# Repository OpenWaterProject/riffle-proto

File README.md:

# riffle_328-proto

The Riffle_328 protoboard is intended to simplify the process of prototyping simple circuits and connecting them to the Riffle_328.  

By plugging it into the 2x7 connector on the end of the Riffle provides access to all 14 pins on the end of the Riffle

- A0
- A1
- A2
- D2
- D3
- D10
- D11
- D12
- SCL
- SDA
- 3v3
- Ground
- Battery voltage

Holes are not connected along the longest dimension of the protoboard; the holes *are* connected with small surface traces along the shortest dimension of the board, but these traces can be cut with a knife if needed.

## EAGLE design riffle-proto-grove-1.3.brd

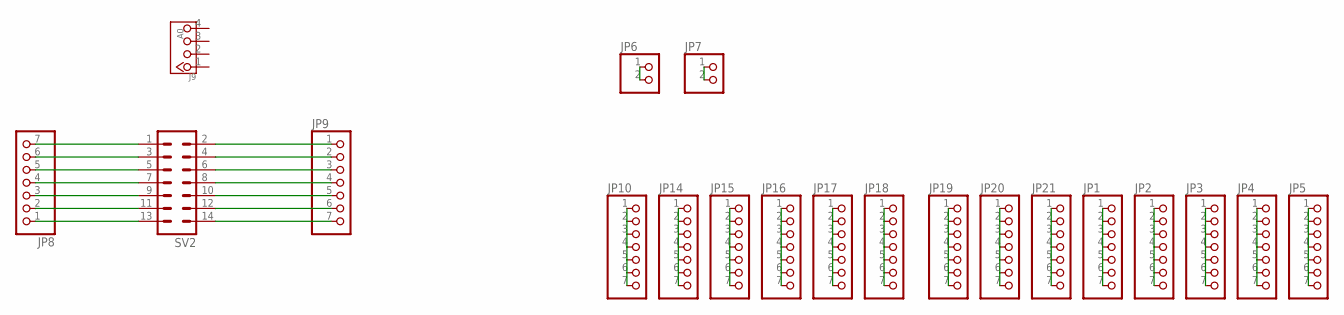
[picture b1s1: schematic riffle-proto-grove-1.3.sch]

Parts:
J9: A0; 4P-2.0-90D
JP1, JP2, JP3, JP4, JP5, JP8, JP9, JP10, JP14, JP15, JP16, JP17, JP18, JP19, JP20, JP21: HEADER-1X770MIL; 1X07_ROUND_70
JP6, JP7: HEADER-1X2ROUND; 1X02_ROUND
SV2: MA07-2

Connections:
D3: JP9.5, SV2.10
GND: JP9.7, SV2.14
unnamed: JP8.1, SV2.13
unnamed: JP8.2, SV2.11
unnamed: JP8.3, SV2.9
unnamed: JP8.4, SV2.7
unnamed: JP8.5, SV2.5
unnamed: JP8.6, SV2.3
unnamed: JP8.7, SV2.1
unnamed: JP10.1, JP10.2, JP10.3, JP10.4, JP10.5, JP10.6, JP10.7
unnamed: JP14.1, JP14.2, JP14.3, JP14.4, JP14.5, JP14.6, JP14.7
unnamed: JP9.3, SV2.6
unnamed: JP9.4, SV2.8
unnamed: JP15.1, JP15.2, JP15.3, JP15.4, JP15.5, JP15.6, JP15.7
unnamed: JP16.1, JP16.2, JP16.3, JP16.4, JP16.5, JP16.6, JP16.7
unnamed: JP17.1, JP17.2, JP17.3, JP17.4, JP17.5, JP17.6, JP17.7
unnamed: JP18.1, JP18.2, JP18.3, JP18.4, JP18.5, JP18.6, JP18.7
unnamed: JP19.1, JP19.2, JP19.3, JP19.4, JP19.5, JP19.6, JP19.7
unnamed: JP20.1, JP20.2, JP20.3, JP20.4, JP20.5, JP20.6, JP20.7
unnamed: JP21.1, JP21.2, JP21.3, JP21.4, JP21.5, JP21.6, JP21.7
unnamed: JP1.1, JP1.2, JP1.3, JP1.4, JP1.5, JP1.6, JP1.7
unnamed: JP2.1, JP2.2, JP2.3, JP2.4, JP2.5, JP2.6, JP2.7
unnamed: JP3.1, JP3.2, JP3.3, JP3.4, JP3.5, JP3.6, JP3.7
unnamed: JP4.1, JP4.2, JP4.3, JP4.4, JP4.5, JP4.6, JP4.7
unnamed: JP5.1, JP5.2, JP5.3, JP5.4, JP5.5, JP5.6, JP5.7
unnamed: JP6.1, JP6.2
unnamed: JP7.1, JP7.2
SCL: JP9.2, SV2.4
SDA: JP9.1, SV2.2
VCC: JP9.6, SV2.12

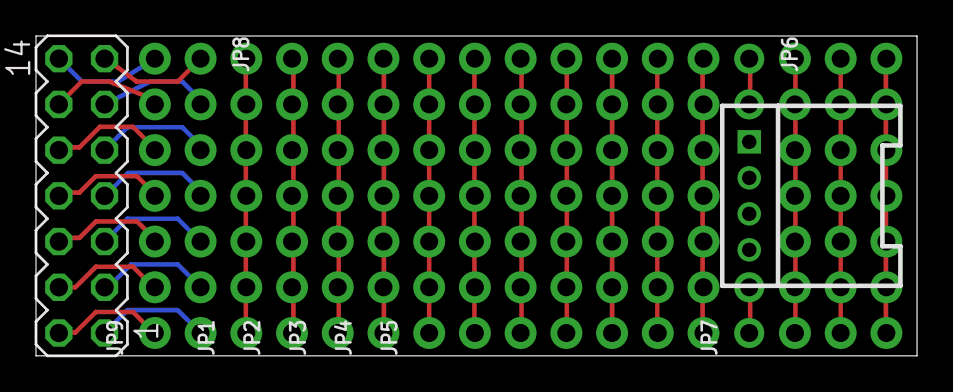
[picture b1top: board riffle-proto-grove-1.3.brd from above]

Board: 2 copper layers, 48.9 x 17.8 mm, 20 parts (0 on the bottom side), 30 nets.

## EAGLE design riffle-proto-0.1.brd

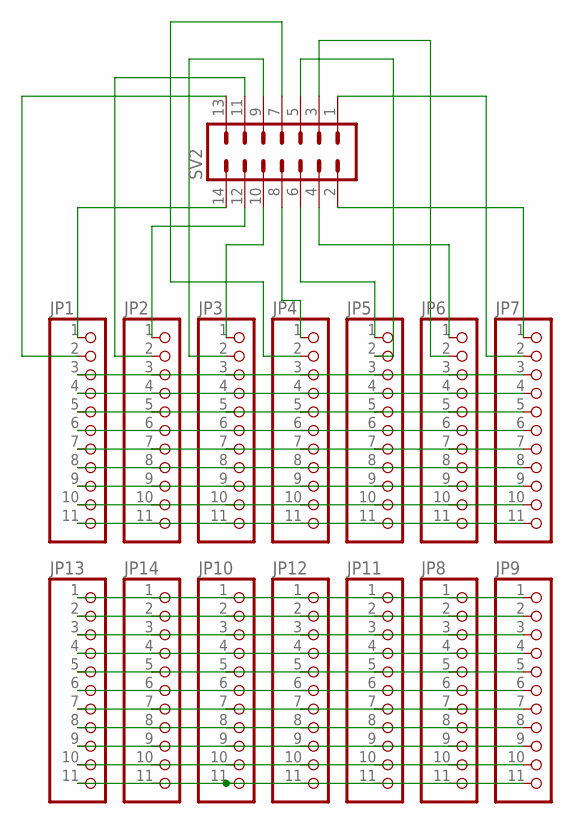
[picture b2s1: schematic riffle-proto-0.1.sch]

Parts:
JP1, JP2, JP3, JP4, JP5, JP6, JP7, JP8, JP9, JP10, JP11, JP12, JP13, JP14: HEADER-1X1176MIL; 1X11_ROUND_76
SV2: MA07-2

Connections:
unnamed: JP1.1, SV2.14
unnamed: JP2.1, SV2.12
unnamed: JP3.1, SV2.10
unnamed: JP4.1, SV2.8
unnamed: JP5.1, SV2.6
unnamed: JP6.1, SV2.4
unnamed: JP7.1, SV2.2
unnamed: JP1.2, SV2.13
unnamed: JP2.2, SV2.11
unnamed: JP3.2, SV2.9
unnamed: JP4.2, SV2.7
unnamed: JP5.2, SV2.5
unnamed: JP6.2, SV2.3
unnamed: JP7.2, SV2.1
unnamed: JP1.3, JP2.3, JP3.3, JP4.3, JP5.3, JP6.3, JP7.3
unnamed: JP1.4, JP2.4, JP3.4, JP4.4, JP5.4, JP6.4, JP7.4
unnamed: JP1.5, JP2.5, JP3.5, JP4.5, JP5.5, JP6.5, JP7.5
unnamed: JP1.6, JP2.6, JP3.6, JP4.6, JP5.6, JP6.6, JP7.6
unnamed: JP1.7, JP2.7, JP3.7, JP4.7, JP5.7, JP6.7, JP7.7
unnamed: JP1.8, JP2.8, JP3.8, JP4.8, JP5.8, JP6.8, JP7.8
unnamed: JP1.9, JP2.9, JP3.9, JP4.9, JP5.9, JP6.9, JP7.9
unnamed: JP1.10, JP2.10, JP3.10, JP4.10, JP5.10, JP6.10, JP7.10
unnamed: JP1.11, JP2.11, JP4.11, JP5.11, JP6.11, JP7.11
unnamed: JP8.1, JP9.1, JP10.1, JP11.1, JP12.1, JP13.1, JP14.1
unnamed: JP8.2, JP9.2, JP10.2, JP11.2, JP12.2, JP13.2, JP14.2
unnamed: JP8.3, JP9.3, JP10.3, JP11.3, JP12.3, JP13.3, JP14.3
unnamed: JP8.4, JP9.4, JP10.4, JP11.4, JP12.4, JP13.4, JP14.4
unnamed: JP8.5, JP9.5, JP10.5, JP11.5, JP12.5, JP13.5, JP14.5
unnamed: JP8.6, JP9.6, JP10.6, JP11.6, JP12.6, JP13.6, JP14.6
unnamed: JP8.7, JP9.7, JP10.7, JP11.7, JP12.7, JP13.7, JP14.7
unnamed: JP8.8, JP9.8, JP10.8, JP11.8, JP12.8, JP13.8, JP14.8
unnamed: JP8.9, JP9.9, JP10.9, JP11.9, JP12.9, JP13.9, JP14.9
unnamed: JP8.10, JP9.10, JP10.10, JP11.10, JP12.10, JP13.10, JP14.10
unnamed: JP8.11, JP9.11, JP10.11, JP11.11, JP12.11, JP13.11, JP14.11

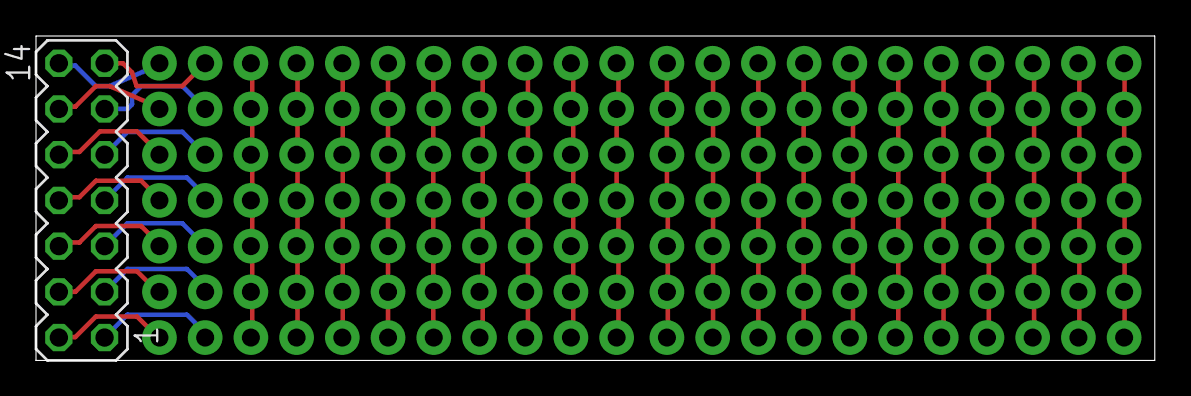
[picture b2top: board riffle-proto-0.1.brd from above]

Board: 2 copper layers, 62.2 x 18.0 mm, 15 parts (0 on the bottom side), 34 nets.
